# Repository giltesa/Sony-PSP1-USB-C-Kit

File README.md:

# Sony PSP 1 USB-C

The **Sony PSP 1: USB-C** is a board that allows to replace the original charging connector for a modern and standard **USB-C**.

**If your original connector is too old or damaged** and you need a new one, or **if you would like to charge your Sony PSP with a standard USB-C charger**, like the charger of your phone, laptop, you can with this board.

This board is compatible with this model:

*   Sony PSP 1000

## Would you like it?

https://shop.giltesa.com/product/sony-psp-1000-usb-c-kit/

## More

- [giltesa.com](https://giltesa.com "giltesa.com")
- [twitter.com](https://twitter.com/giltesa "twitter.com")

## License

This project is licensed under a **Creative Commons** license:
**[Attribution-NonCommercial-ShareAlike 4.0 International (CC BY-NC-SA 4.0) ](https://creativecommons.org/licenses/by-nc-sa/4.0/)**

Check the [LICENSE.md](LICENSE.md) for more information.

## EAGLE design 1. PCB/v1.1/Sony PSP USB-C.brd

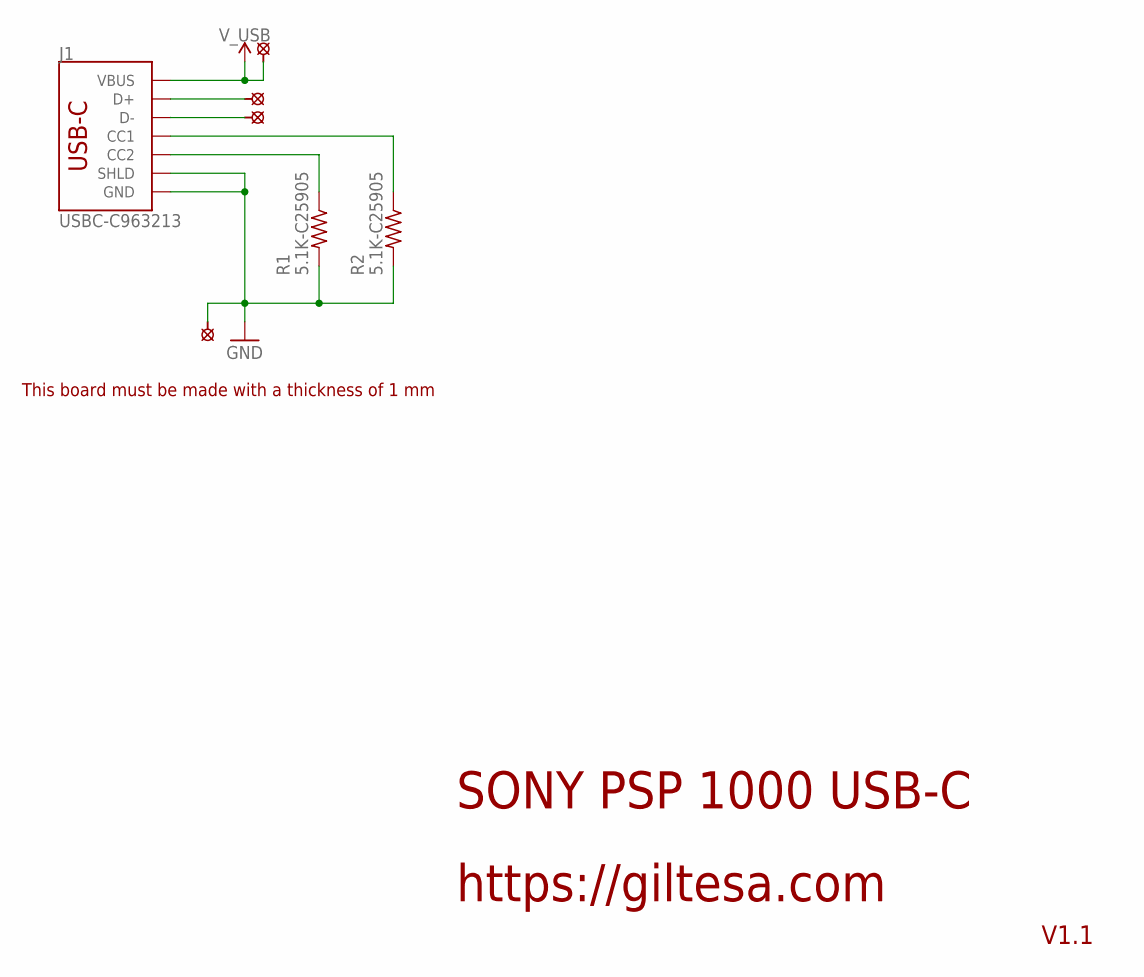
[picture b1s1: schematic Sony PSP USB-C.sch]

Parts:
J1: USBC-C963213; USB-C_18P_SLIM_GT-USB-7025
R1, R2: 5.1K-C25905; R0402
U$1, U$3: SOLDER_PAD_PSP_1000; PSP_1000_PAD
U$5, U$6: SOLDER_PAD-1.2; SOLDER_PAD_1.2

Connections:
CC1: J1.A5-CC1 (CC1), R2.1
CC2: J1.B5-CC2 (CC2), R1.1
D+: J1.A6-DP1 (D+), J1.B6-DP2 (D+), U$5.P$1
D-: J1.A7-DN1 (D-), J1.B7-DN2 (D-), U$6.P$1
GND: J1.A1-GND (GND), J1.A12-GND (GND), J1.B1-GND (GND), J1.B12-GND (GND), J1.GND1 (GND), J1.GND2 (GND), J1.SHLD1 (SHLD), J1.SHLD2 (SHLD), J1.SHLD3 (SHLD), J1.SHLD4 (SHLD), R1.2, R2.2, U$1.1
V_USB: J1.A4-VBUS (VBUS), J1.A9-VBUS (VBUS), J1.B4-VBUS (VBUS), J1.B9-VBUS (VBUS), U$3.1

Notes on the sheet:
SONY PSP 1000 USB-C
https://giltesa.com
V1.1
This board must be made with a thickness of 1 mm

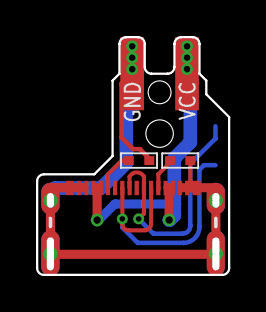
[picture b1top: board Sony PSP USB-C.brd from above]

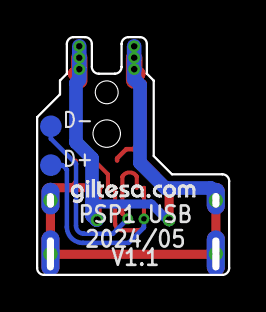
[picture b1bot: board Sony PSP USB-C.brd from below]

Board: 2 copper layers, 10.4 x 12.9 mm, 8 parts (3 on the bottom side), 6 nets.

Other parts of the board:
U$11: GILTESA.COM_MASK_7MM

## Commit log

2024-05-25 no message
2024-10-10 v1.0
2024-10-10 v1.1

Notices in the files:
parts and their libraries:
SparkFun: Licensing: CC v3.0 Share-Alike You are welcome to use this library for commercial purposes.
SparkFun-PowerSymbols: Licensing: Creative Commons ShareAlike 4.0 International - https://creativecommons.org/licenses/by-sa/4.0
